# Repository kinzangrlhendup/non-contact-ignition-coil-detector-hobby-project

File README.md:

# Non-Contact Ignition-Coil Firing Detector

A development-stage, open-hardware automotive diagnostic tool that senses the electromagnetic transient produced when an ignition coil fires—without connecting directly to the high-voltage secondary circuit.

The detector combines a PCB meander pickup, input protection, an envelope detector, an adjustable LM393 comparator, and a transistor-driven LED and active buzzer.

[View the schematic](images/kicad-schematic.png) · [Read the circuit design](docs/circuit-design.md) · [Review the simulation](docs/simulation-results.md) · [See the PCB record](docs/pcb-design.md) · [Watch the 3D preview](media/kicad-3d-board-preview.mp4)

## What it does

The board is intended to indicate the **presence of ignition-coil firing** on coil-on-plug systems, including the types commonly used in Maruti Suzuki, Hyundai and KIA vehicles.

A positive indication means that the detector sensed a nearby transient. It does **not** measure secondary voltage, spark duration or spark energy, and it cannot by itself prove that a coil is healthy under cylinder pressure.

> **Development status:** The signal-conditioning and detection stages have been simulated, and the KiCad PCB and fabrication outputs have been prepared. A physical prototype has not yet been assembled, calibrated or tested on a vehicle.

## Design highlights

- Non-contact electric-field pickup using a front-copper PCB meander
- 10 kΩ input-current limiting and 1N4148 pulse rectification
- 3.3 V Zener clamp for comparator-input protection
- 100 nF / 470 kΩ envelope detector with a nominal 47 ms time constant
- Adjustable detection threshold using an LM393-family comparator
- Comparator hysteresis to reduce switching chatter
- PN2222A alarm driver
- Visual LED and audible 5 V active-buzzer indication
- 9 V battery input, reverse-polarity protection and regulated 5 V rail
- Through-hole, two-layer KiCad PCB intended for accessible prototype assembly

## Functional chain

```text
Ignition-coil transient
        ↓ capacitive/electric-field coupling
PCB meander pickup
        ↓
Protection and rectification
        ↓
Envelope detector and 3.3 V clamp
        ↓
Adjustable LM393 comparator
        ↓
PN2222A driver
        ↓
LED + active buzzer
```

## Project status

| Stage | Status |
| --- | --- |
| Circuit concept | Completed |
| LTspice functional simulation | Completed; transient baseline verified on 18 July 2026 |
| KiCad schematic | Completed; user-run ERC reported clean |
| PCB layout | Completed; user-run DRC reported clean |
| Gerber and drill generation | Completed and visually reviewed on 18 July 2026 |
| Physical assembly | Not started |
| Bench calibration | Not performed |
| Vehicle testing | Not performed |

Gerber and Excellon files are provided in [`manufacturing/gerbers/`](manufacturing/gerbers/) for design review and first-prototype fabrication. They should not be treated as production-validated outputs.

## Verified LTspice baseline

The archived transient simulation uses a 0–3 V ideal pulse stimulus at 10 Hz. Under the recorded test condition:

| Signal | Approximate result |
| --- | --- |
| Regulated supply | 5.002 V |
| Adjustable threshold | 1.04–1.05 V |
| Envelope peak | 1.60–1.65 V |
| Comparator output high | 3.95 V |
| Comparator output low | 0.15–0.20 V |
| Simulated load current | 22–23 mA when active |

Five correct detection events were observed during the 500 ms run.

The result verifies the downstream envelope, comparator and alarm-driver behaviour for the selected ideal input. It does not establish the signal amplitude that a real PCB pickup will receive from a particular ignition coil or sensing distance. Full results and interpretation are documented in [`docs/simulation-results.md`](docs/simulation-results.md).

## Repository guide

| Path | Contents |
| --- | --- |
| [`ltspice/`](ltspice/) | LTspice source, comparator model dependencies and retained solver log |
| [`kicad/`](kicad/) | Native KiCad 10 schematic, PCB and project files |
| [`docs/`](docs/) | Circuit explanation, PCB record, simulation results and test procedure |
| [`images/`](images/) | Schematics, PCB views and simulation plots |
| [`bom/`](bom/) | Preliminary bill of materials |
| [`manufacturing/gerbers/`](manufacturing/gerbers/) | Gerber job, copper, mask, silkscreen, outline and drill files |
| [`media/`](media/) | KiCad 3D board-preview video |

## Reviewing or reproducing the design

1. Read the [circuit-design notes](docs/circuit-design.md) and [known limitations](#known-limitations).
2. Open [`ltspice/09_final_ignition_coil_detector.asc`](ltspice/09_final_ignition_coil_detector.asc) to reproduce the archived functional simulation.
3. Open [`kicad/Ignition_Coil_Detector.kicad_pro`](kicad/Ignition_Coil_Detector.kicad_pro) in KiCad 10 to review the schematic and PCB.
4. Check every selected component against the [preliminary BOM](bom/bill_of_materials.csv), particularly footprint, pinout, polarity and voltage rating.
5. Refill copper zones and rerun ERC and DRC after any design change.
6. Re-export and independently inspect all Gerber and drill files before ordering a PCB.
7. Follow the staged [prototype testing procedure](docs/testing-procedure.md), beginning with unpowered inspection and a current-limited bench supply.

Proposed first-prototype construction: two-layer FR-4, 1.6 mm thickness, 1 oz copper, green solder mask and white silkscreen.

## Known limitations

- The LTspice baseline uses an ideal voltage pulse rather than a physical capacitive-coupling model.
- The simulation uses an LT1117-5 model, while the KiCad design uses an L7805.
- Two simulated supply capacitors are recorded as `10m` (10 mF in LTspice), whereas the PCB uses 10 µF parts.
- The PCB pickup sensitivity has not been measured against sensing distance, orientation or different coil constructions.
- Rejection of injector, alternator, starter-motor, relay and adjacent-coil interference has not been established.
- The design has not been validated for automotive load dump, thermal cycling, vibration, moisture or EMC compliance.
- Firing detection alone cannot identify every weak or load-dependent ignition-coil fault.

These points are documented so that simulation evidence is not mistaken for completed hardware validation.

## Planned next steps

- Synchronize the LTspice and KiCad power-supply implementations
- Model and sweep capacitive pickup coupling
- Verify purchased-component footprints and pinouts
- Assemble the first PCB prototype
- Characterize detection distance, orientation and sensitivity
- Test noise rejection and adjacent-coil selectivity
- Compare responses from multiple known-good and suspect ignition coils
- Document measured results and revise the design

## Safety

Automotive ignition systems can produce hazardous high-voltage pulses.

- Use this detector only as a non-contact instrument.
- Never connect the pickup to an ignition-coil secondary terminal or spark-plug conductor.
- Use an insulated enclosure before engine-bay testing.
- Keep the PCB, hands, clothing and test leads away from hot or moving engine components.
- Use suitable high-voltage precautions for any controlled bench ignition-coil test.
- Treat this project as an experimental prototype, not a certified diagnostic instrument.

## Feedback and contributions

Technical review, test results and constructive criticism are welcome. If you build or modify the design, please document the coil type, sensing distance, orientation, operating conditions and component changes so results can be compared meaningfully.

## Author

Designed by **Kinzang R. Lhendup**  
First PCB design and fabrication project · July 2026

## Citation and licence

If you refer to, reproduce or adapt this project, please cite:

> Lhendup, K. R. (2026). *Non-Contact Ignition-Coil Firing Detector* (Version 0.1.0) [Hardware design and simulation project]. GitHub. https://github.com/kinzangrlhendup/non-contact-ignition-coil-detector-hobby-project

Citation metadata is available in [`CITATION.cff`](CITATION.cff).

The original hardware design is licensed under [CERN-OHL-S-2.0](LICENSE). Please retain the attribution and notices required by the licence. The Texas Instruments comparator simulation model remains subject to its own terms, described in [`THIRD_PARTY_NOTICES.md`](THIRD_PARTY_NOTICES.md).

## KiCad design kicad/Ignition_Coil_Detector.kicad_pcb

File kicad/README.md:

# KiCad project

This directory contains the native KiCad 10.0 project sources imported on 18 July 2026:

```text
Ignition_Coil_Detector.kicad_pro
Ignition_Coil_Detector.kicad_sch
Ignition_Coil_Detector.kicad_pcb
```

The project uses standard KiCad libraries, while the board file embeds its placed footprints and graphical content. Open `Ignition_Coil_Detector.kicad_pro` to load the complete project.

KiCad lock files and the user-specific `.kicad_prl` file were intentionally excluded. They are session/local-interface state and are not portable design sources.

The design was created with KiCad 10.0. Earlier KiCad releases may refuse to open or may not preserve the files correctly.

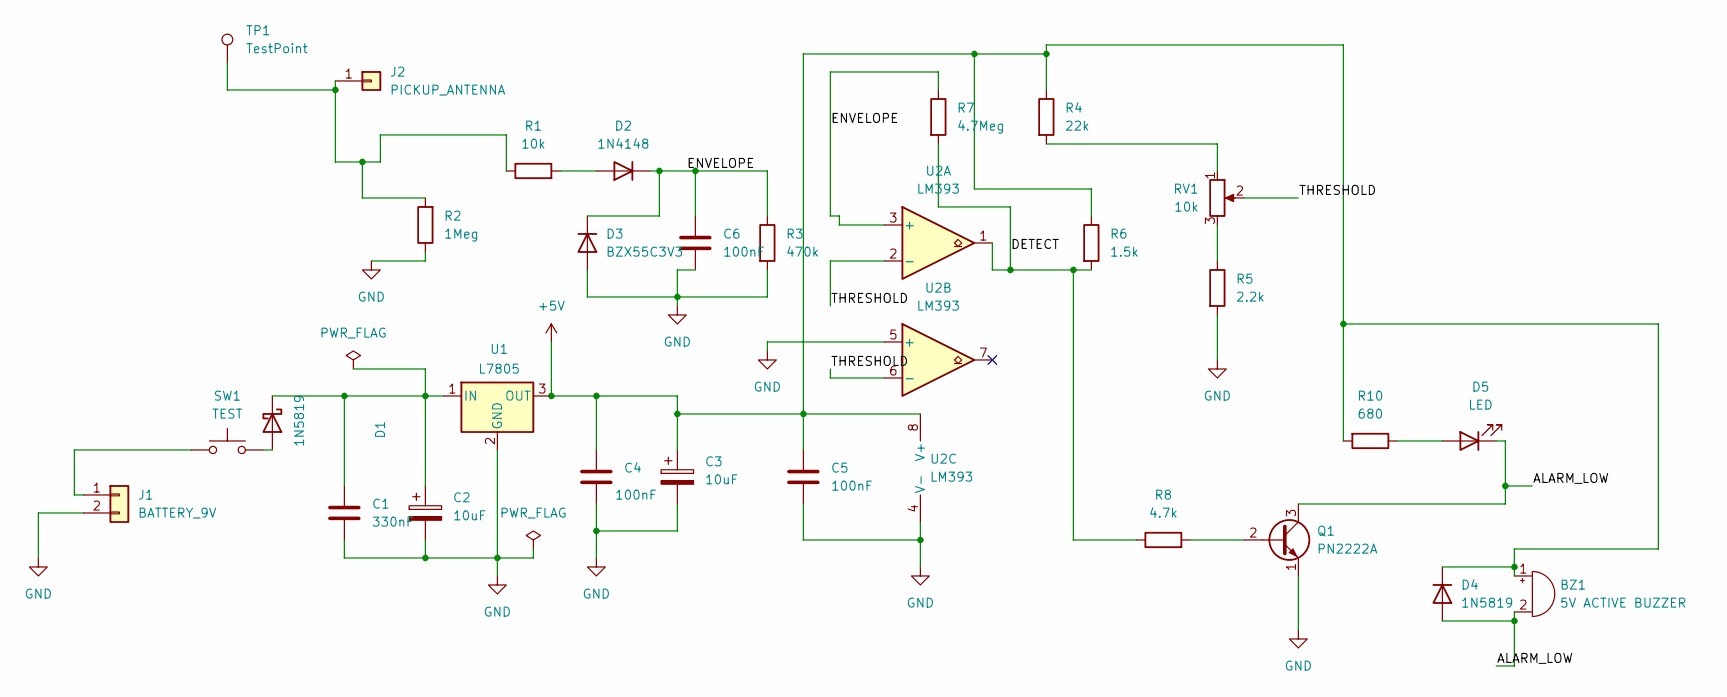
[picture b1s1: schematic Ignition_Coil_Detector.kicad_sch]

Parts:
BZ1: 5V ACTIVE BUZZER; Buzzer_12x9.5RM7.6
C1: 330nF; C_Disc_D5.0mm_W2.5mm_P5.00mm
C2, C3: 10uF; CP_Radial_D5.0mm_P2.00mm
C4, C5, C6: 100nF; C_Disc_D5.0mm_W2.5mm_P5.00mm
D1, D4: 1N5819; D_DO-41_SOD81_P10.16mm_Horizontal
D2: 1N4148; D_DO-35_SOD27_P10.16mm_Horizontal
D3: BZX55C3V3; D_DO-35_SOD27_P10.16mm_Horizontal
D5: LED; LED_D5.0mm
J1: BATTERY_9V; TerminalBlock_Phoenix_MKDS-1,5-2-5.08_1x02_P5.08mm_Horizont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
J2: PICKUP_ANTENNA; PinHeader_1x01_P2.54mm_Vertical
Q1: PN2222A; TO-92_Inline
R1: 10k; R_Axial_DIN0207_L6.3mm_D2.5mm_P10.16mm_Horizontal
R2: 1Meg; R_Axial_DIN0207_L6.3mm_D2.5mm_P10.16mm_Horizontal
R3: 470k; R_Axial_DIN0207_L6.3mm_D2.5mm_P10.16mm_Horizontal
R4: 22k; R_Axial_DIN0207_L6.3mm_D2.5mm_P10.16mm_Horizontal
R5: 2.2k; R_Axial_DIN0207_L6.3mm_D2.5mm_P10.16mm_Horizontal
R6: 1.5k; R_Axial_DIN0207_L6.3mm_D2.5mm_P10.16mm_Horizontal
R7: 4.7Meg; R_Axial_DIN0207_L6.3mm_D2.5mm_P10.16mm_Horizontal
R8: 4.7k; R_Axial_DIN0207_L6.3mm_D2.5mm_P10.16mm_Horizontal
R10: 680; R_Axial_DIN0207_L6.3mm_D2.5mm_P10.16mm_Horizontal
RV1: 10k; Potentiometer_Bourns_3296W_Vertical
SW1: TEST; SW_PUSH_6mm_H5mm
TP1: TestPoint; TestPoint_Pad_D3.0mm
U1: L7805; TO-220-3_Vertical
U2: LM393; DIP-8_W7.62mm

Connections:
+5V: BZ1.1 (+), C3.1, C4.1, C5.1, D4.1 (K), R4.1, R6.1, R10.2, U1.3 (OUT), U2.8 (V+)
/ALARM_LOW: BZ1.2 (-), D4.2 (A), D5.1 (K), Q1.3 (C)
/DETECT: R6.2, R7.2, R8.1, U2.1
/ENVELOPE: C6.1, D2.1 (K), D3.1 (K), R3.1, R7.1, U2.3 (+)
/THRESHOLD: RV1.2, U2.2 (-), U2.6 (-)
GND: C1.2, C2.2, C3.2, C4.2, C5.2, C6.2, D3.2 (A), J1.2, Q1.1 (E), R2.1, R3.2, R5.2, U1.2 (GND), U2.4 (V-), U2.5 (+)
unnamed: D1.2 (A), SW1.2
unnamed: C1.1, C2.1, D1.1 (K), U1.1 (IN)
unnamed: D2.2 (A), R1.2
unnamed: D5.2 (A), R10.1
unnamed: J1.1, SW1.1
unnamed: J2.1 (Pin_1_1), R1.1, R2.2, TP1.1 (1_1)
unnamed: Q1.2 (B), R8.2
unnamed: R4.2, RV1.1
unnamed: R5.1, RV1.3

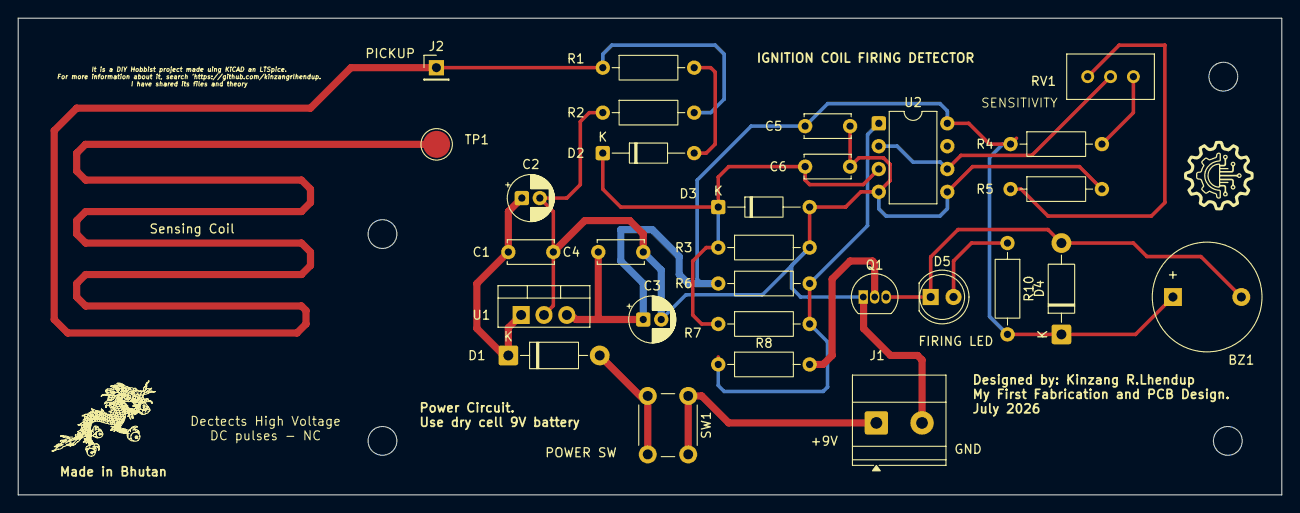
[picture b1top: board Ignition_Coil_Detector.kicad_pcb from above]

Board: 2 copper layers, 140.5 x 53.0 mm, 29 parts (0 on the bottom side), 15 nets.

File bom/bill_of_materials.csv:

Reference,Quantity,Value/Part,Function,Status/Note
J1,1,9 V battery connector,Power input,Verify footprint
SW1,1,Normally-open momentary pushbutton,Hold-to-test power control,Verify selected 6 mm footprint
D1,1,1N5819,Reverse-polarity protection,KiCad design
U1,1,L7805,5 V regulator,KiCad design differs from LTspice LT1117-5
C1,1,330 nF,Regulator input bypass,Verify against native KiCad schematic
C2,1,10 uF,Input bulk capacitance,Verify polarity and footprint
C3,1,10 uF,Output bulk capacitance,Verify polarity and footprint
C4-C5,2,100 nF,Supply decoupling,Verify references in KiCad
J2,1,Pickup connector,PCB meander/external pickup connection,Verify footprint
TP1,1,Test point,Raw pickup monitoring,KiCad design
R1,1,10 kOhm,Input current limiting,KiCad design
R2,1,1 MOhm,Raw-input bleed,Final value requires sensitivity validation
D2,1,1N4148,Input rectifier,KiCad design
D3,1,BZX55C3V3,3.3 V input clamp,Verify axial footprint and polarity
C6,1,100 nF,Envelope storage,KiCad design
R3,1,470 kOhm,Envelope discharge,KiCad design
U2,1,LM393,Dual comparator,Verify DIP pin mapping and unused section
R4,1,22 kOhm,Threshold-divider upper resistor,KiCad design
RV1,1,10 kOhm,Sensitivity adjustment,Verify pin order and footprint
R5,1,2.2 kOhm,Threshold-divider lower resistor,KiCad design
R6,1,1.5 kOhm,Comparator output pull-up,KiCad design
R7,1,4.7 MOhm,Comparator hysteresis feedback,KiCad design
R8,1,4.7 kOhm,Transistor base resistor,KiCad design
Q1,1,PN2222A,Alarm driver,Verify E-B-C footprint pinout
R10,1,680 Ohm,LED current limiting,KiCad design
D5,1,LED,Firing indicator,Choose colour and verify polarity
BZ1,1,5 V active buzzer,Audible indicator,Verify current and polarity
D4,1,1N5819,Buzzer transient suppression,Verify need and polarity
